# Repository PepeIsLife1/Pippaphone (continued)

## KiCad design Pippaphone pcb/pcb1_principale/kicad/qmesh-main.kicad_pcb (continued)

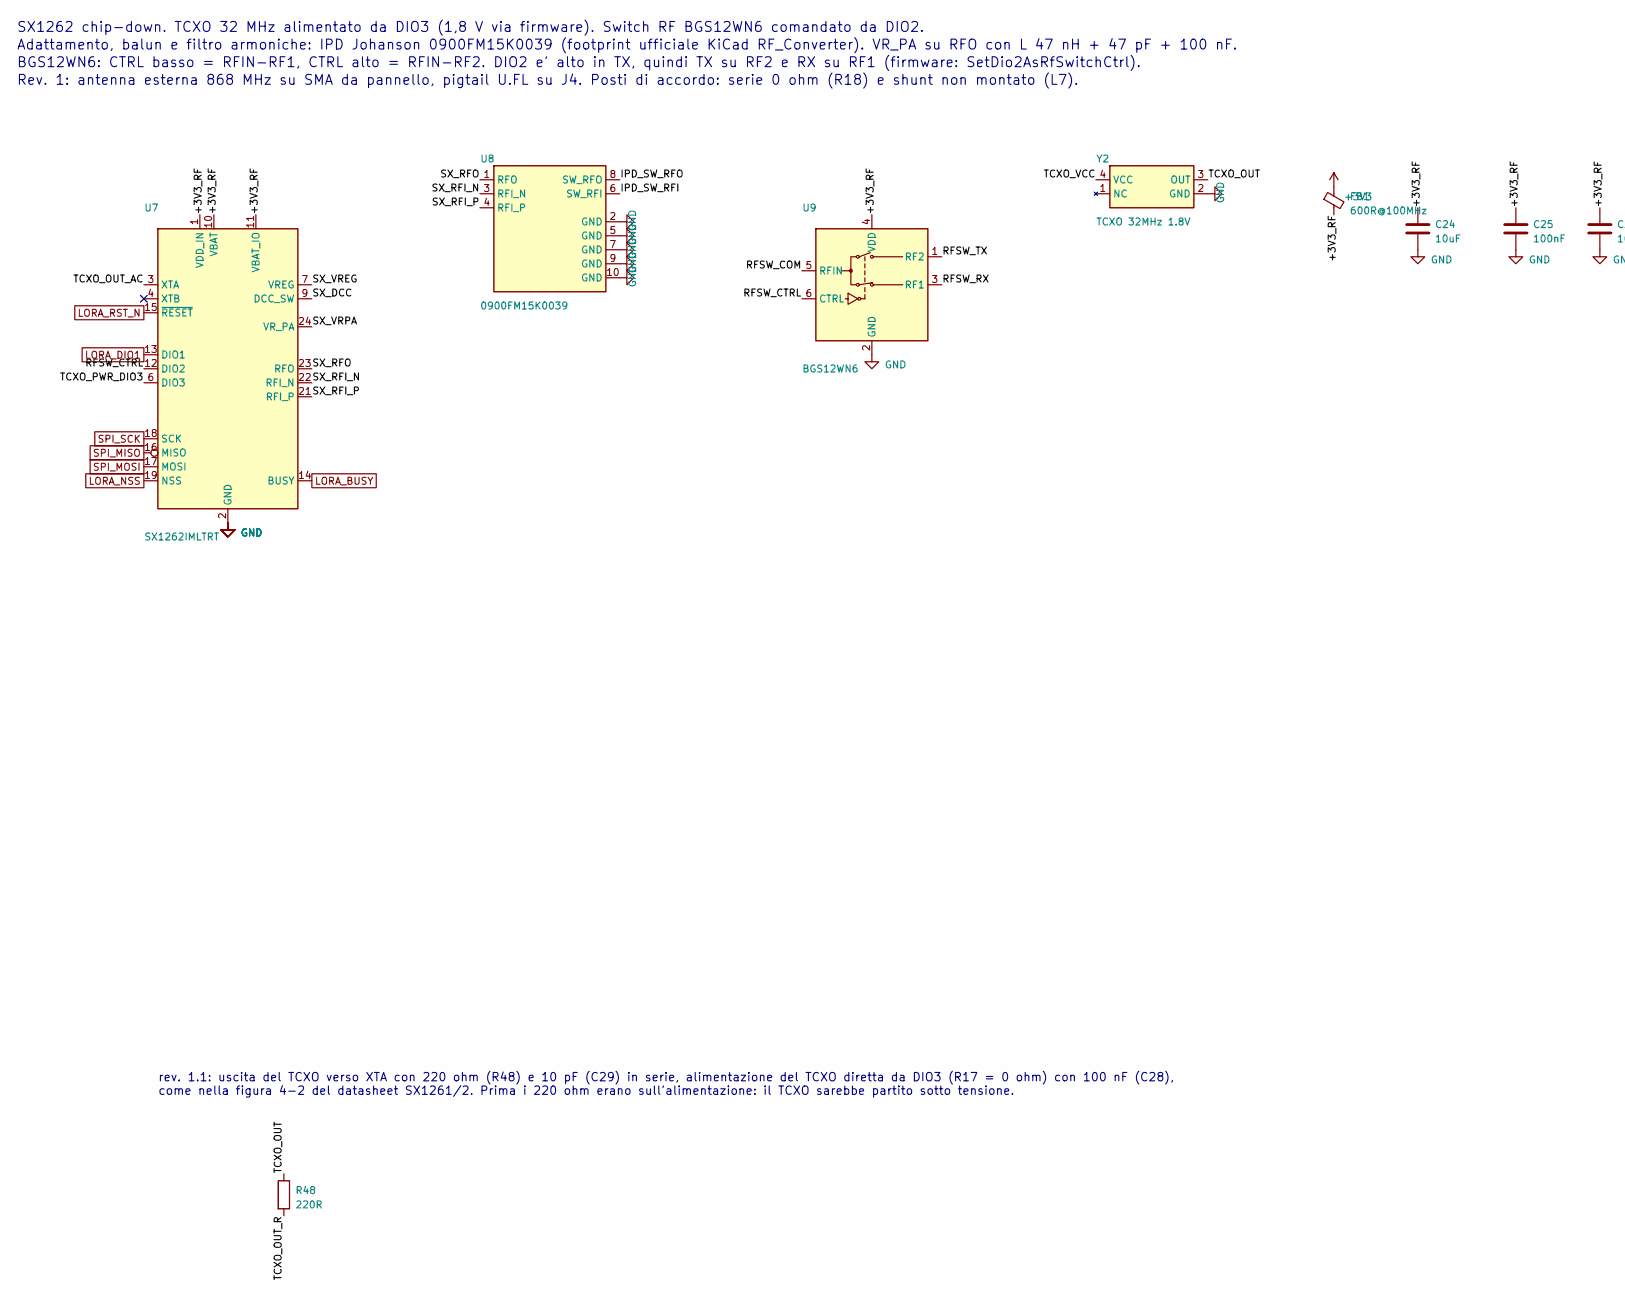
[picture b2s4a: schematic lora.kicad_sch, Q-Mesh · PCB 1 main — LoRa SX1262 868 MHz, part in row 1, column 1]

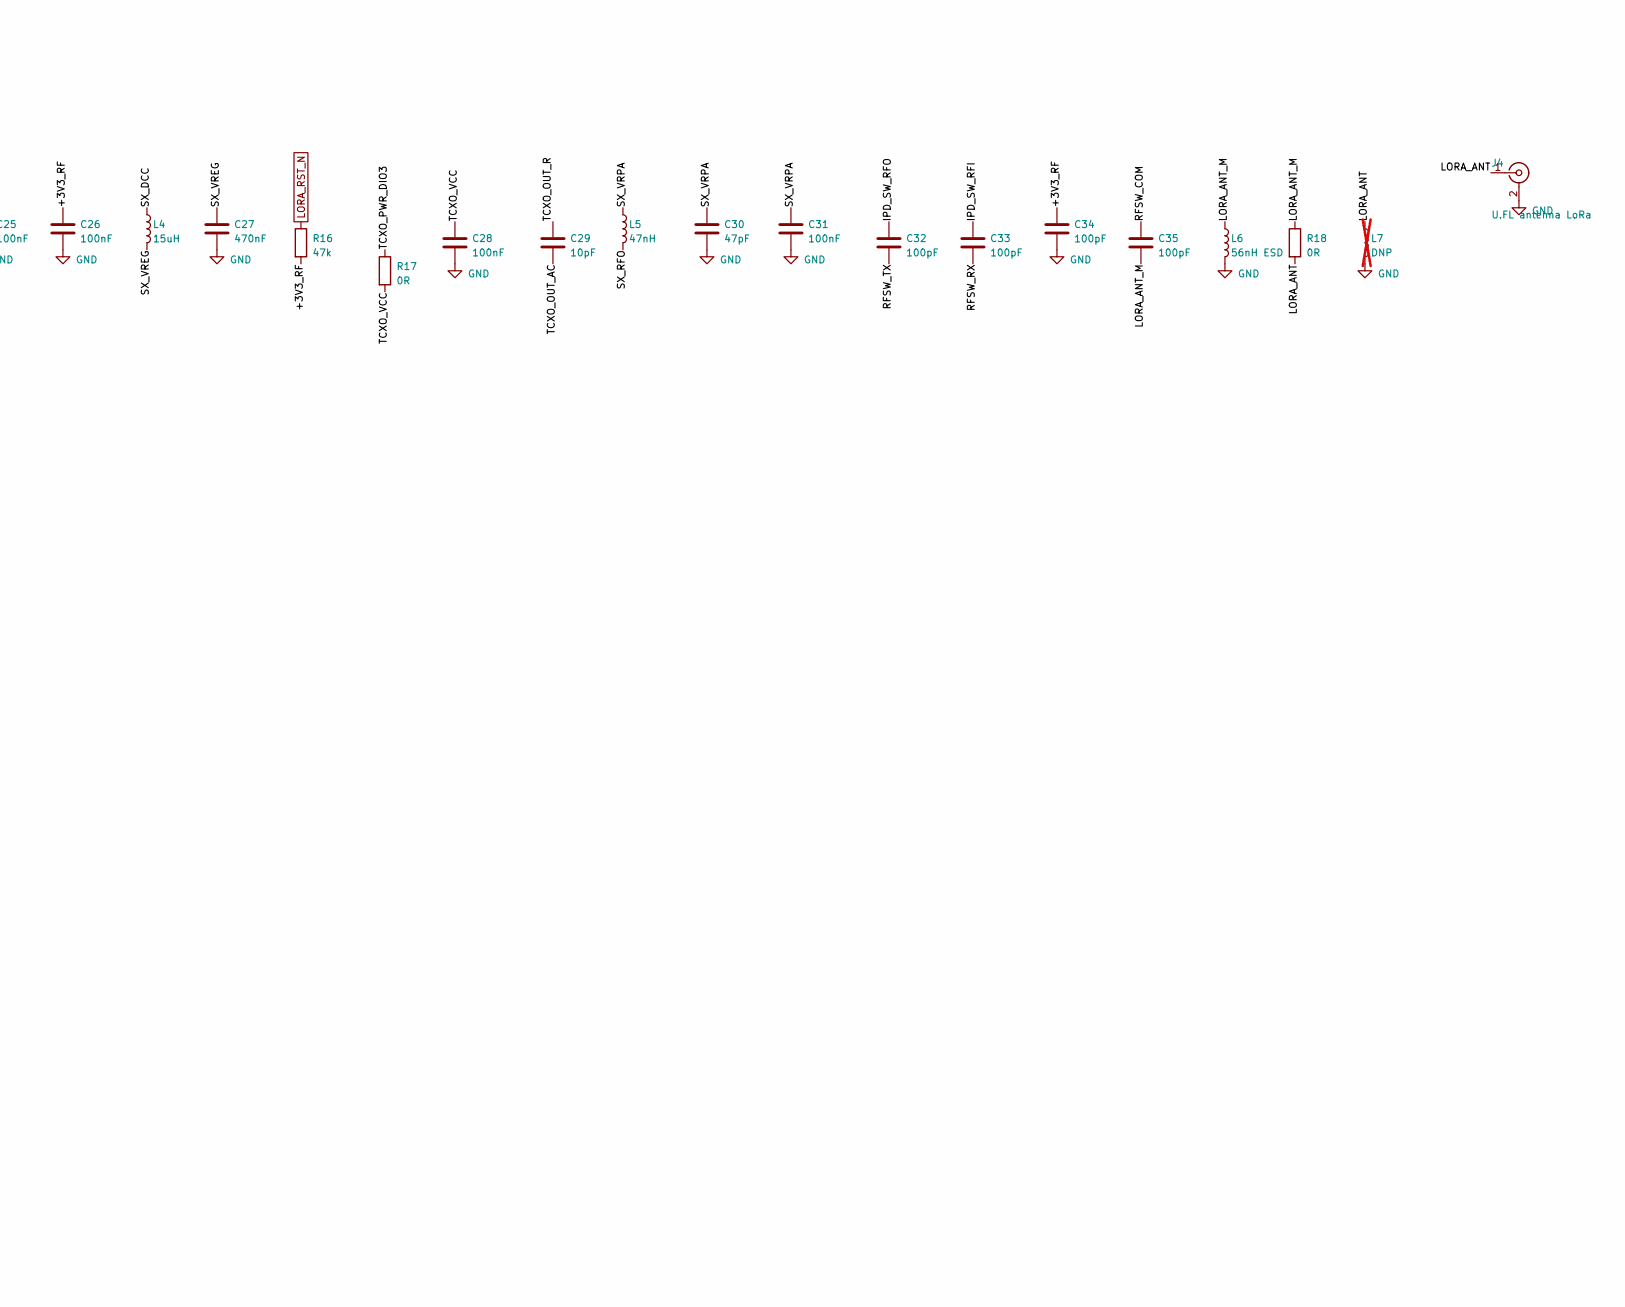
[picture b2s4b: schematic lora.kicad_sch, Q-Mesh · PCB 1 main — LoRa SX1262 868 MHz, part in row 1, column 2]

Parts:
C24: 10uF; C_0603_1608Metric
C25, C26, C28, C31: 100nF; C_0402_1005Metric
C27: 470nF; C_0402_1005Metric
C29: 10pF; C_0402_1005Metric
C30: 47pF; C_0402_1005Metric
C32, C33, C34, C35: 100pF; C_0402_1005Metric
FB1: 600R@100MHz; L_0402_1005Metric; MPN BLM15AG601SN1D
J4: U.FL antenna LoRa; U.FL_Hirose_U.FL-R-SMT-1_Vertical; MPN U.FL-R-SMT-1(80)
L4: 15uH; L_0805_2012Metric; MPN MLZ2012N150LT000
L5: 47nH; L_0402_1005Metric; MPN LQG15HS47NJ02
L6: 56nH ESD; L_0402_1005Metric
L7: DNP; L_0402_1005Metric; not fitted
R16: 47k; R_0402_1005Metric
R17, R18: 0R; R_0402_1005Metric
R48: 220R; R_0402_1005Metric; MPN 0402WGF2200TCE
U7: SX1262IMLTRT; QFN-24-1EP_4x4mm_P0.5mm_EP2.6x2.6mm; MPN SX1262IMLTRT
U8: 0900FM15K0039; Balun_Johanson_0900FM15K0039; MPN 0900FM15K0039001E
U9: BGS12WN6; Infineon_PG-TSNP-6-10_0.7x1.1mm_0.7x1.1mm_P0.4mm; MPN BGS12WN6E6327XTSA1
Y2: TCXO 32MHz 1.8V; Oscillator_SMD_SeikoEpson_TG2520SMN-xxx-xxxxxx-4Pin_2.5x2.0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; MPN X1G0054210205

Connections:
+3V3: FB1.1; also elsewhere on the board
+3V3_RF: C24.1, C25.1, C26.1, C34.1, FB1.2, R16.2, U7.1 (VDD_IN), U7.10 (VBAT), U7.11 (VBAT_IO), U9.4 (VDD)
GND: C24.2, C25.2, C26.2, C27.2, C28.2, C30.2, C31.2, C34.2, J4.2 (Ext), L6.2, L7.2, U7.2 (GND), U7.5 (GND), U7.8 (GND), U7.20 (GND), U7.25 (GND), U8.2 (GND), U8.5 (GND), U8.7 (GND), U8.9 (GND), U8.10 (GND), U9.2 (GND), Y2.2 (GND); also elsewhere on the board
IPD_SW_RFI: C33.1, U8.6 (SW_RFI)
IPD_SW_RFO: C32.1, U8.8 (SW_RFO)
LORA_ANT: J4.1 (In), L7.1, R18.2
LORA_ANT_M: C35.2, L6.1, R18.1
LORA_BUSY: U7.14 (BUSY); also elsewhere on the board
LORA_DIO1: U7.13 (DIO1); also elsewhere on the board
LORA_NSS: U7.19 (NSS); also elsewhere on the board
LORA_RST_N: R16.1, U7.15 (~RESET); also elsewhere on the board
RFSW_COM: C35.1, U9.5 (RFIN)
RFSW_CTRL: U7.12 (DIO2), U9.6 (CTRL)
RFSW_RX: C33.2, U9.3 (RF1)
RFSW_TX: C32.2, U9.1 (RF2)
SPI_MISO: U7.16 (MISO); also elsewhere on the board
SPI_MOSI: U7.17 (MOSI); also elsewhere on the board
SPI_SCK: U7.18 (SCK); also elsewhere on the board
SX_DCC: L4.1, U7.9 (DCC_SW)
SX_RFI_N: U7.22 (RFI_N), U8.3 (RFI_N)
SX_RFI_P: U7.21 (RFI_P), U8.4 (RFI_P)
SX_RFO: L5.2, U7.23 (RFO), U8.1 (RFO)
SX_VREG: C27.1, L4.2, U7.7 (VREG)
SX_VRPA: C30.1, C31.1, L5.1, U7.24 (VR_PA)
TCXO_OUT: R48.1, Y2.3 (OUT)
TCXO_OUT_AC: C29.2, U7.3 (XTA)
TCXO_OUT_R: C29.1, R48.2
TCXO_PWR_DIO3: R17.1, U7.6 (DIO3)
TCXO_VCC: C28.1, R17.2, Y2.4 (VCC)

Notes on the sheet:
SX1262 chip-down. TCXO 32 MHz alimentato da DIO3 (1,8 V via firmware). Switch RF BGS12WN6 comandato da DIO2.
Adattamento, balun e filtro armoniche: IPD Johanson 0900FM15K0039 (footprint ufficiale KiCad RF_Converter). VR_PA su RFO con L 47 nH + 47 pF + 100 nF.
BGS12WN6: CTRL basso = RFIN-RF1, CTRL alto = RFIN-RF2. DIO2 e' alto in TX, quindi TX su RF2 e RX su RF1 (firmware: SetDio2AsRfSwitchCtrl).
Rev. 1: antenna esterna 868 MHz su SMA da pannello, pigtail U.FL su J4. Posti di accordo: serie 0 ohm (R18) e shunt non montato (L7).
rev. 1.1: uscita del TCXO verso XTA con 220 ohm (R48) e 10 pF (C29) in serie, alimentazione del TCXO diretta da DIO3 (R17 = 0 ohm) con 100 nF (C28), come nella figura 4-2 del datasheet SX1261/2. Prima i 220 ohm erano sull'alimentazione: il TCXO sarebbe partito sotto tensione.

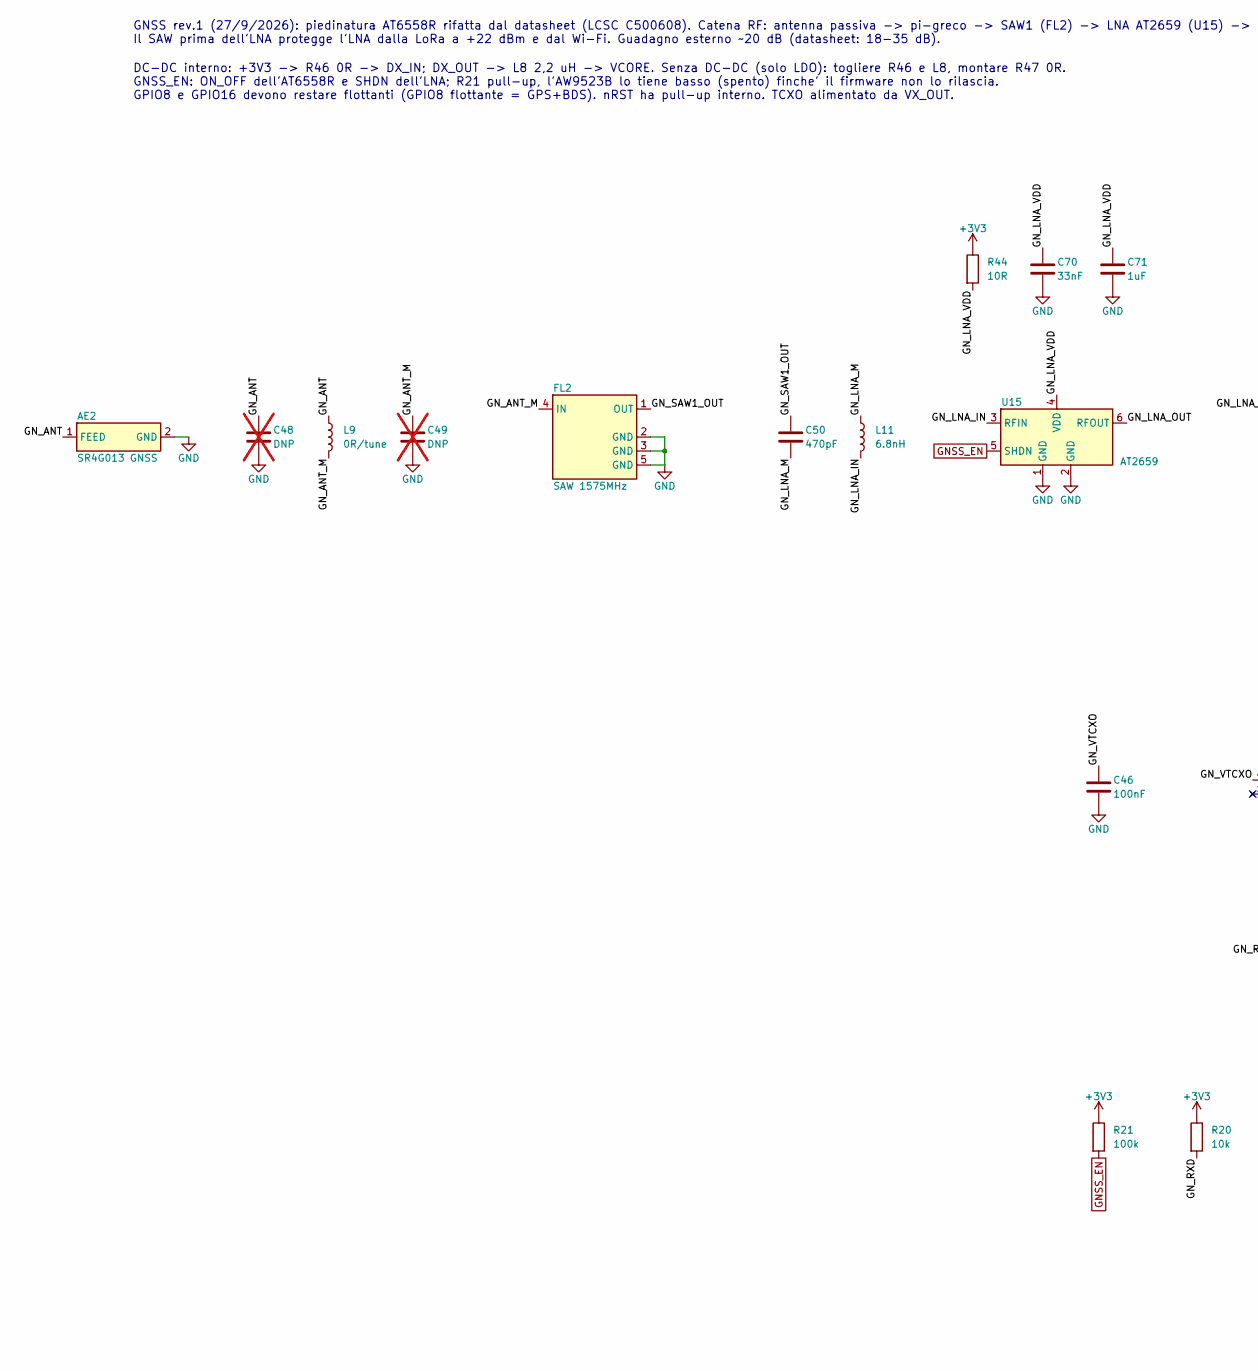
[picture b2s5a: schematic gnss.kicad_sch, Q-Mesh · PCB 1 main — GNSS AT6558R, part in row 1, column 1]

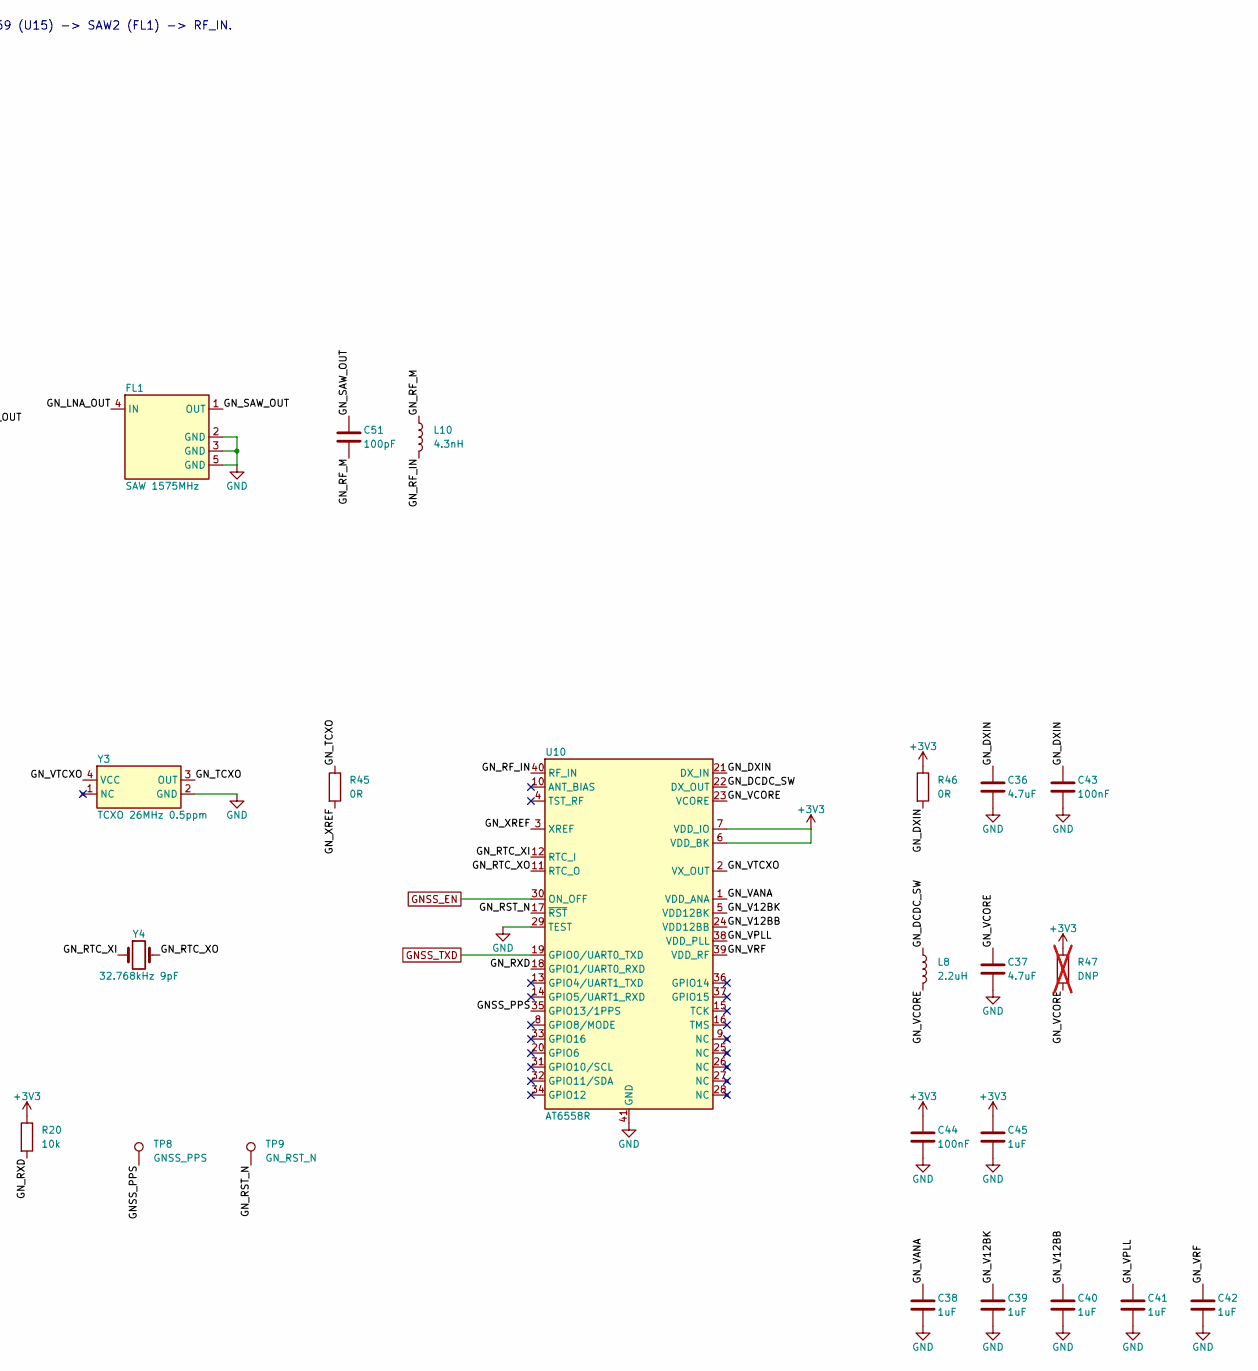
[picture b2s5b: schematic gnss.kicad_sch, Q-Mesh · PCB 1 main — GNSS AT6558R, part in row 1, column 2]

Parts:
AE2: SR4G013 GNSS; Antenova_SR4G013_GPS; MPN Antenova SR4G013
C36, C37: 4.7uF; C_0603_1608Metric
C38, C39, C40, C41, C42, C45, C71: 1uF; C_0402_1005Metric
C43, C44, C46: 100nF; C_0402_1005Metric
C48, C49: DNP; C_0402_1005Metric; not fitted
C50: 470pF; C_0402_1005Metric
C51: 100pF; C_0402_1005Metric
C70: 33nF; C_0402_1005Metric; MPN CL05B333KO5NNNC
FL1, FL2: SAW 1575MHz; Filter_1411-5_1.4x1.1mm; MPN B39162B4327P810
L8: 2.2uH; L_0603_1608Metric; MPN LQM18PN2R2MFRL
L9: 0R/tune; L_0402_1005Metric
L10: 4.3nH; L_0402_1005Metric; MPN LQG15HS4N3S02D
L11: 6.8nH; L_0402_1005Metric; MPN LQG15HS6N8J02D
R20: 10k; R_0402_1005Metric
R21: 100k; R_0402_1005Metric
R44: 10R; R_0402_1005Metric
R45, R46: 0R; R_0402_1005Metric
R47: DNP; R_0402_1005Metric; not fitted
TP8: GNSS_PPS; TestPoint_Pad_D1.0mm
TP9: GN_RST_N; TestPoint_Pad_D1.0mm
U10: AT6558R; QFN-40-1EP_5x5mm_P0.4mm_EP3.6x3.6mm; MPN AT6558R-5N32
U15: AT2659; AT2659_DFN-6_1.5x1.0mm_P0.5mm; MPN AT2659
Y3: TCXO 26MHz 0.5ppm; Oscillator_SMD_SeikoEpson_TG2520SMN-xxx-xxxxxx-4Pin_2.5x2.0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; MPN 2T026000VY
Y4: 32.768kHz 9pF; Crystal_SMD_2012-2Pin_2.0x1.2mm; MPN SC-20S 32.768kHz 20PPM 9pF

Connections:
+3V3: C44.1, C45.1, R20.1, R21.1, R44.1, R46.1, R47.1, U10.6 (VDD_BK), U10.7 (VDD_IO); also elsewhere on the board
GND: AE2.2 (GND), C36.2, C37.2, C38.2, C39.2, C40.2, C41.2, C42.2, C43.2, C44.2, C45.2, C46.2, C48.2, C49.2, C70.2, C71.2, FL1.2 (GND), FL1.3 (GND), FL1.5 (GND), FL2.2 (GND), FL2.3 (GND), FL2.5 (GND), U10.29 (TEST), U10.41 (GND), U15.1 (GND), U15.2 (GND), Y3.2 (GND); also elsewhere on the board
GNSS_EN: R21.2, U10.30 (ON_OFF), U15.5 (SHDN); also elsewhere on the board
GNSS_PPS: TP8.1, U10.35 (GPIO13/1PPS)
GNSS_TXD: U10.19 (GPIO0/UART0_TXD); also elsewhere on the board
GN_ANT: AE2.1 (FEED), C48.1, L9.1
GN_ANT_M: C49.1, FL2.4 (IN), L9.2
GN_DCDC_SW: L8.1, U10.22 (DX_OUT)
GN_DXIN: C36.1, C43.1, R46.2, U10.21 (DX_IN)
GN_LNA_IN: L11.2, U15.3 (RFIN)
GN_LNA_M: C50.2, L11.1
GN_LNA_OUT: FL1.4 (IN), U15.6 (RFOUT)
GN_LNA_VDD: C70.1, C71.1, R44.2, U15.4 (VDD)
GN_RF_IN: L10.2, U10.40 (RF_IN)
GN_RF_M: C51.2, L10.1
GN_RST_N: TP9.1, U10.17 (~RST)
GN_RTC_XI: U10.12 (RTC_I), Y4.1
GN_RTC_XO: U10.11 (RTC_O), Y4.2
GN_RXD: R20.2, U10.18 (GPIO1/UART0_RXD)
GN_SAW1_OUT: C50.1, FL2.1 (OUT)
GN_SAW_OUT: C51.1, FL1.1 (OUT)
GN_TCXO: R45.1, Y3.3 (OUT)
GN_V12BB: C40.1, U10.24 (VDD12BB)
GN_V12BK: C39.1, U10.5 (VDD12BK)
GN_VANA: C38.1, U10.1 (VDD_ANA)
GN_VCORE: C37.1, L8.2, R47.2, U10.23 (VCORE)
GN_VPLL: C41.1, U10.38 (VDD_PLL)
GN_VRF: C42.1, U10.39 (VDD_RF)
GN_VTCXO: C46.1, U10.2 (VX_OUT), Y3.4 (VCC)
GN_XREF: R45.2, U10.3 (XREF)

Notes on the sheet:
GNSS rev.1 (27/9/2026): piedinatura AT6558R rifatta dal datasheet (LCSC C500608). Catena RF: antenna passiva -> pi-greco -> SAW1 (FL2) -> LNA AT2659 (U15) -> SAW2 (FL1) -> RF_IN. Il SAW prima dell'LNA protegge l'LNA dalla LoRa a +22 dBm e dal Wi-Fi. Guadagno esterno ~20 dB (datasheet: 18-35 dB).
DC-DC interno: +3V3 -> R46 0R -> DX_IN; DX_OUT -> L8 2,2 uH -> VCORE. Senza DC-DC (solo LDO): togliere R46 e L8, montare R47 0R. GNSS_EN: ON_OFF dell'AT6558R e SHDN dell'LNA; R21 pull-up, l'AW9523B lo tiene basso (spento) finche' il firmware non lo rilascia. GPIO8 e GPIO16 devono restare flottanti 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

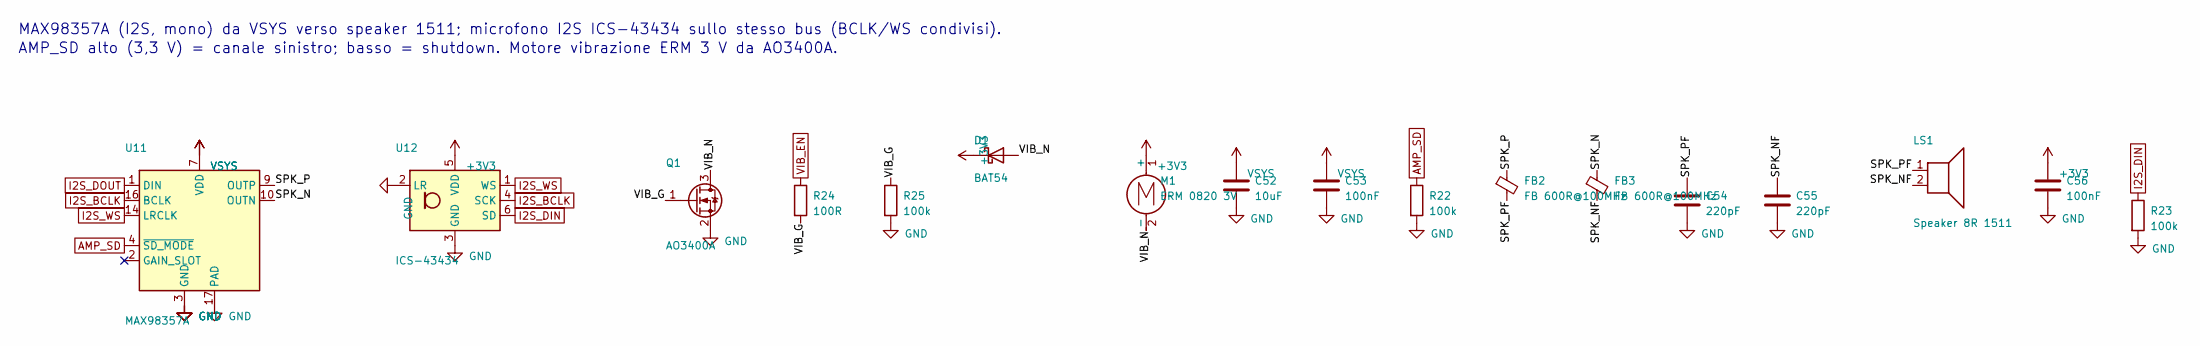
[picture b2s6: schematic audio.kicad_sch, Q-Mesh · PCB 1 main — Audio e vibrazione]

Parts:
C52: 10uF; C_0603_1608Metric
C53, C56: 100nF; C_0402_1005Metric
C54, C55: 220pF; C_0402_1005Metric
D1: BAT54; D_SOD-323; MPN BAT54WS-7-F
FB2, FB3: FB 600R@100MHz; L_0402_1005Metric
LS1: Speaker 8R 1511; Speaker_Pads_2x; MPN Speaker 15x11x3 8ohm
M1: ERM 0820 3V; Motor_Pads_2x; MPN Coin vibration motor 8x2 mm 3V
Q1: AO3400A; SOT-23; MPN AO3400A
R22, R23, R25: 100k; R_0402_1005Metric
R24: 100R; R_0402_1005Metric
U11: MAX98357A; TQFN-16-1EP_3x3mm_P0.5mm_EP1.23x1.23mm; MPN MAX98357AETE+T
U12: ICS-43434; InvenSense_ICS-43434-6_3.5x2.65mm; MPN ICS-43434

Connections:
+3V3: C56.1, D1.1 (K), M1.1 (+), U12.5 (VDD); also elsewhere on the board
AMP_SD: R22.1, U11.4 (~SD_MODE); also elsewhere on the board
GND: C52.2, C53.2, C54.2, C55.2, C56.2, Q1.2 (S), R22.2, R23.2, R25.2, U11.3 (GND), U11.11 (GND), U11.15 (GND), U11.17 (PAD), U12.2 (LR), U12.3 (GND); also elsewhere on the board
I2S_BCLK: U11.16 (BCLK), U12.4 (SCK); also elsewhere on the board
I2S_DIN: R23.1, U12.6 (SD); also elsewhere on the board
I2S_DOUT: U11.1 (DIN); also elsewhere on the board
I2S_WS: U11.14 (LRCLK), U12.1 (WS); also elsewhere on the board
SPK_N: FB3.1, U11.10 (OUTN)
SPK_NF: C55.1, FB3.2, LS1.2
SPK_P: FB2.1, U11.9 (OUTP)
SPK_PF: C54.1, FB2.2, LS1.1
VIB_EN: R24.1; also elsewhere on the board
VIB_G: Q1.1 (G), R24.2, R25.1
VIB_N: D1.2 (A), M1.2 (-), Q1.3 (D)
VSYS: C52.1, C53.1, U11.7 (VDD), U11.8 (VDD); also elsewhere on the board

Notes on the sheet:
MAX98357A (I2S, mono) da VSYS verso speaker 1511; microfono I2S ICS-43434 sullo stesso bus (BCLK/WS condivisi).
AMP_SD alto (3,3 V) = canale sinistro; basso = shutdown. Motore vibrazione ERM 3 V da AO3400A.

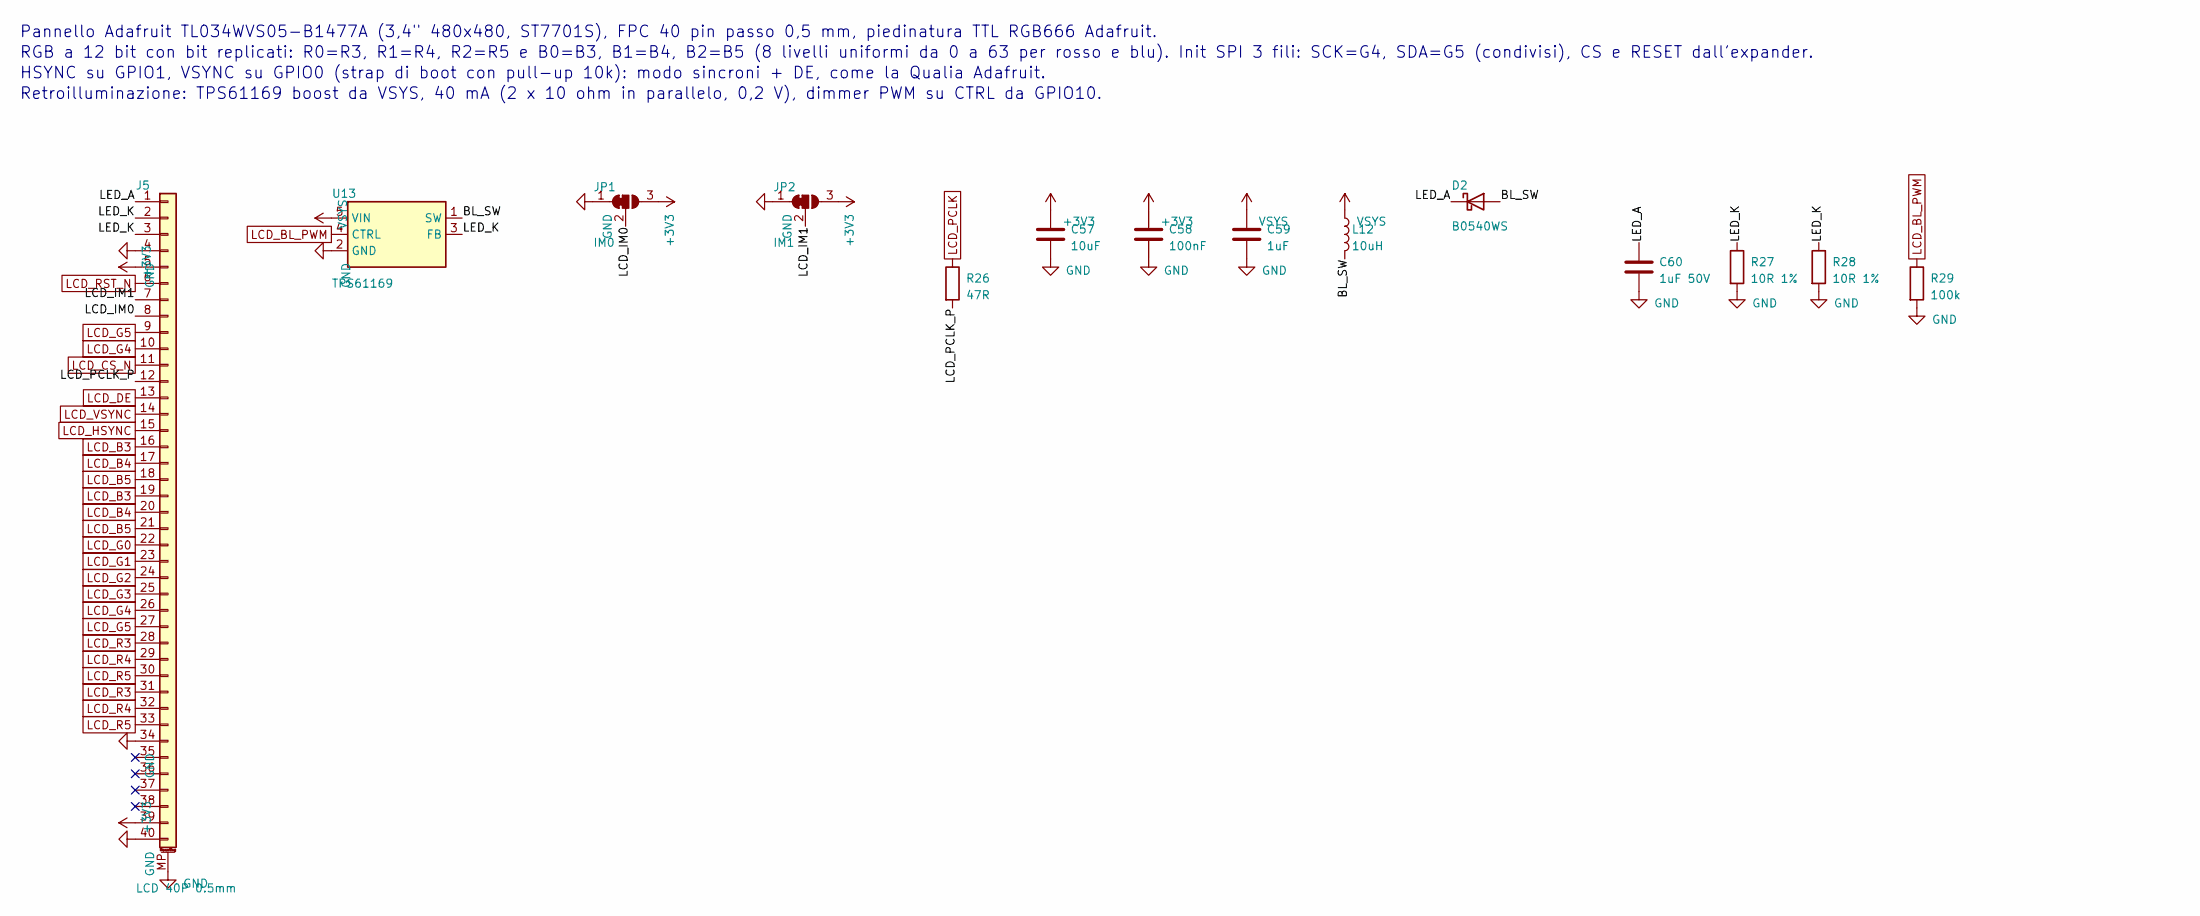
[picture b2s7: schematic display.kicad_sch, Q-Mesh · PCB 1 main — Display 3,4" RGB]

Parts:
C57: 10uF; C_0603_1608Metric
C58: 100nF; C_0402_1005Metric
C59: 1uF; C_0603_1608Metric
C60: 1uF 50V; C_0805_2012Metric
D2: B0540WS; D_SOD-323; MPN B0540WS SF
J5: LCD 40P 0.5mm; Hirose_FH12-40S-0.5SH_1x40-1MP_P0.50mm_Horizontal; MPN Hirose FH12A-40S-0.5SH(55)
JP1: IM0; SolderJumper-3_P1.3mm_Bridged12_RoundedPad1.0x1.5mm
JP2: IM1; SolderJumper-3_P1.3mm_Bridged12_RoundedPad1.0x1.5mm
L12: 10uH; L_Changjiang_FNR252012S; MPN FTC252012S100MBCA
R26: 47R; R_0402_1005Metric
R27, R28: 10R 1%; R_0402_1005Metric
R29: 100k; R_0402_1005Metric
U13: TPS61169; SOT-353_SC-70-5; MPN TPS61169DCKR

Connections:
+3V3: C57.1, C58.1, J5.5, J5.39, JP1.3 (B), JP2.3 (B); also elsewhere on the board
BL_SW: D2.2 (A), L12.2, U13.1 (SW)
GND: C57.2, C58.2, C59.2, C60.2, J5.4, J5.34, J5.40, J5.MP (MountPin), JP1.1 (A), JP2.1 (A), R27.2, R28.2, R29.2, U13.2 (GND); also elsewhere on the board
LCD_B3: J5.16, J5.19; also elsewhere on the board
LCD_B4: J5.17, J5.20; also elsewhere on the board
LCD_B5: J5.18, J5.21; also elsewhere on the board
LCD_BL_PWM: R29.1, U13.4 (CTRL); also elsewhere on the board
LCD_CS_N: J5.11; also elsewhere on the board
LCD_DE: J5.13; also elsewhere on the board
LCD_G0: J5.22; also elsewhere on the board
LCD_G1: J5.23; also elsewhere on the board
LCD_G2: J5.24; also elsewhere on the board
LCD_G3: J5.25; also elsewhere on the board
LCD_G4: J5.10, J5.26; also elsewhere on the board
LCD_G5: J5.9, J5.27; also elsewhere on the board
LCD_HSYNC: J5.15; also elsewhere on the board
LCD_IM0: J5.8, JP1.2 (C)
LCD_IM1: J5.7, JP2.2 (C)
LCD_PCLK: R26.1; also elsewhere on the board
LCD_PCLK_P: J5.12, R26.2
LCD_R3: J5.28, J5.31; also elsewhere on the board
LCD_R4: J5.29, J5.32; also elsewhere on the board
LCD_R5: J5.30, J5.33; also elsewhere on the board
LCD_RST_N: J5.6; also elsewhere on the board
LCD_VSYNC: J5.14; also elsewhere on the board
LED_A: C60.1, D2.1 (K), J5.1
LED_K: J5.2, J5.3, R27.1, R28.1, U13.3 (FB)
VSYS: C59.1, L12.1, U13.5 (VIN); also elsewhere on the board

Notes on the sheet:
Pannello Adafruit TL034WVS05-B1477A (3,4" 480x480, ST7701S), FPC 40 pin passo 0,5 mm, piedinatura TTL RGB666 Adafruit.
RGB a 12 bit con bit replicati: R0=R3, R1=R4, R2=R5 e B0=B3, B1=B4, B2=B5 (8 livelli uniformi da 0 a 63 per rosso e blu). Init SPI 3 fili: SCK=G4, SDA=G5 (condivisi), CS e RESET dall'expander.
HSYNC su GPIO1, VSYNC su GPIO0 (strap di boot con pull-up 10k): modo sincroni + DE, come la Qualia Adafruit.
Retroilluminazione: TPS61169 boost da VSYS, 40 mA (2 x 10 ohm in parallelo, 0,2 V), dimmer PWM su CTRL da GPIO10.
